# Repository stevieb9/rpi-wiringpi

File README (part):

NAME
    RPi::WiringPi - Perl interface to Raspberry Pi's board, GPIO, LCDs and
    other various items

SYNOPSIS
    Please see the FAQ for full usage details.

        use RPi::WiringPi;
        use RPi::Const qw(:all);
 
        my $pi = RPi::WiringPi->new;
 
        # For the below handful of system methods, see RPi::SysInfo
 
        my $mem_percent = $pi->mem_percent;
        my $cpu_percent = $pi->cpu_percent;
        my $cpu_temp    = $pi->core_temp;
        my $gpio_info   = $pi->gpio_info;
        my $raspi_conf  = $pi->raspi_config;
        my $net_info    = $pi->network_info;
        my $file_system = $pi->file_system;
        my $hw_details  = $pi->pi_details;
        my $pi_model    = $pi->pi_model;

        # Pin
 
        my $pin = $pi->pin(5);
        $pin->mode(OUTPUT);
        $pin->write(ON);
 
        my $num     = $pin->num;
        my $mode    = $pin->mode;
        my $state   = $pin->read;
 
        # Cleanup all pins and reset them to default before exiting your program
 
        $pi->cleanup;

DESCRIPTION
    This is the root module for the "RPi::WiringPi" system. It interfaces to
    a Raspberry Pi board, its accessories and its GPIO pins via the wiringPi
    <http://wiringpi.com> library through the Perl wrapper WiringPi::API
    <https://metacpan.org/pod/WiringPi::API> module, and various other
    custom device specific modules.

    wiringPi <http://wiringpi.com> must be installed prior to
    installing/using this module (v3.18).

    We always and only use the "GPIO" pin numbering scheme.

    This module is essentially a 'manager' for the sub-modules (ie.
    components). You can use the component modules directly, but retrieving
    components through this module instead has many benefits. We maintain a
    registry of pins and other data, and reset the Pi back to default
    settings when your program ends (on normal exit, on an uncaught die(),
    and on "SIGINT"/"SIGTERM"), so components are not left in an
    inconsistent state. Component modules do none of these things.

    There are a basic set of constants that can be imported. See RPi::Const.

    It's handy to have access to a pin mapping conversion chart. There's an
    excellent pin scheme map for reference at pinout.xyz
    <https://pinout.xyz/pinout/wiringpi>. You can also run the "pinmap"
    command that was installed by this module, or "wiringPi"'s "gpio
    readall" command.

BASE METHODS
  new([%args])
    Returns a new "RPi::WiringPi" object. We exclusively use the "GPIO"
    (Broadcom (BCM) GPIO) pin numbering scheme.

    Parameters:

        setup => $string

    Optional, String: Which "wiringPi" setup routine (and therefore pin
    numbering scheme) to initialize the board with. Matching is
    case-insensitive on the first letter:

        'gpio'      - GPIO (BCM) numbering; the default if not sent in
        'wiringpi'  - wiringPi's own (WPI) numbering
        'none'      - skip board setup entirely (the pin scheme remains
                      uninitialized; primarily for testing)

    Any other value will croak. Note that if another application in the
    process has already run a setup routine (signalled via the
    "RPI_PIN_MODE" environment variable), that existing scheme is honoured
    and this parameter is ignored.

        shm_key => $string

    By default, we use the key "rpiw" as the shared memory segment key. You
    can change this if desired. Useful for separating "groups" of Pi objects
    from one another (for example, production scripts can operate at the
    same time as test scripts, and both use their own shared memory pool).

        fatal_exit => $bool

    Optional: Controls what happens when we trap a "SIGINT" (Ctrl-C) or
    "SIGTERM". In both cases we first reset the Pi hardware to a safe state.
    By default ("fatal_exit" true), we then re-raise the signal so the
    program terminates as it normally would. Set "fatal_exit" to false (0)
    to perform the cleanup and then continue running your script (eg. for
    unit-test work, or to allow your own signal handling to take over).

    With multiple Pi objects in a single process, the signal is re-raised
    only if every live object has "fatal_exit" true; any object created with
    "fatal_exit => 0" keeps the process running.

    Note that this only affects trapped signals. Hardware cleanup on a
    normal exit or on an uncaught die() always happens automatically (via
    the object's "END"/ "DESTROY" handling); we do not trap $SIG{__DIE__},
    so a die() you catch yourself with "eval" will not disturb your pins.
    Any $SIG{INT}/$SIG{TERM} handler you installed before creating the
    object is chained to, not replaced.

        rpi_register => $bool

    Optional: Set this value to false (0) to bypass the Pi object
    registration in the meta data. This will also prevent pins from being
    registered as well. If set to false, no object or pin cleanup will take
    place at the end of a program run.

        rpi_register_pins => $bool

    Optional: Similar to "rpi_register", but only bypasses the pin
    registration. Object registration will still occur, and the object will
    be cleaned up after but the pins will not. Should only be used for
    testing.

  adc
    There are two different ADCs that you can select from. The default is
    the ADS1x15 series:

   ADS1115
    Returns a RPi::ADC::ADS object, which allows you to read the four analog
    input channels on an Adafruit ADS1xxx analog to digital converter.

    Parameters:

    The default (no parameters) is almost always enough, but please do
    review the documentation in the link above for further information, and
    have a look at the ADC tutorial section in this distribution.

   MCP3008
    You can also use an RPi::ADC::MCP3008 ADC.

    Parameters:

        model => 'MCP3008'

    Mandatory, String. The exact quoted string above.

        channel => $channel

    Mandatory, Integer. 0 or 1 for the Pi's onboard hardware CS/SS CE0 and
    CE1 pins, or any GPIO number above 1 in order to use an arbitrary GPIO
    pin for the CS pin, and we'll do the bit-banging of the SPI bus
    automatically.

  bmp
    Returns a RPi::BMP180 object, which allows you to return the current
    temperature in farenheit or celcius, along with the ability to retrieve
    the barometric pressure in kPa.

  dac
    Returns a RPi::DAC::MCP4922 object (supports all 49x2 series DACs).
    These chips provide analog output signals from the Pi's digital output.
    Please see the documentation of that module for further information on
    both the configuration and use of the DAC object.

    Parameters:

        model => 'MCP4922'

    Optional, String. The model of the DAC you're using. Defaults to
    "MCP4922".

        channel => 0|1

    Mandatory, Bool. The SPI channel to use.

        cs => $pin

    Mandatory, Integer. A valid GPIO pin that the DAC's Chip Select is
    connected to.

    There are a handful of other parameters that aren't required. For those,
    please refer to the RPi::DAC::MCP4922 documentation.

  dpot($cs, $channel)
    Returns a RPi::DigiPot::MCP4XXXX object, which allows you to manage a
    digital potentiometer (only the MCP4XXXX versions are currently
    supported).

    See the linked documentation for full documentation on usage, or the
    RPi::WiringPi::FAQ for usage examples.

  gps
    Returns a GPSD::Parse object, allowing you to track your location.

    The GPS distribution requires "gpsd" to be installed and running. All
    parameters for the GPS can be sent in here and we'll pass them along.
    Please see the link above for the full documentation on that module.

  hcsr04($trig, $echo)
    Returns a RPi::HCSR04 ultrasonic distance measurement sensor object,
    allowing you to retrieve the distance from the sensor in inches,
    centimetres or raw data.

    Parameters:

        $trig

    Mandatory, Integer: The trigger pin number, in GPIO numbering scheme.

        $echo

    Mandatory, Integer: The echo pin number, in GPIO numbering scheme.

  hygrometer($pin)
    Returns a RPi::DHT11 temperature/humidity sensor object, allows you to
    fetch the temperature (celcius or farenheit) as well as the current
    humidity level.

    Parameters:

        $pin

    Mandatory, Integer: The GPIO pin the sensor is connected to.

  i2c($addr, [$device])
    Creates a new RPi::I2C device object which allows you to communicate
    with the devices on an I2C bus.

    See the linked documentation for full documentation on usage, or the
    RPi::WiringPi::FAQ for usage examples.

    Aruino note: If using I2C with an Arduino, the Pi may speak faster than
    the Arduino can. If this is the case, try lowering the I2C bus speed on
    the Pi:

        dtparam=i2c_arm_baudrate=10000

  lcd(...)
    Returns a RPi::LCD object, which allows you to fully manipulate LCD
    displays connected to your Raspberry Pi.

    Please see the linked documentation for information regarding the
    parameters required.

  oled([$model], [$i2c_addr], [$display_splash_page])
    Returns a specific "RPi::OLED::SSD1306" OLED display object, allowing
    you to display text, characters and shapes to the screen.

    Currently, only the "128x64" size model is offered, see the
    RPi::OLED::SSD1306::128_64 documentation for full usage details.

    Parameters:

        $model

    Optional, String: The screen size of the OLED you've got. Valid options
    are "128x64", "128x32" and "96x16". Currently, only the "128x64" option
    is valid, and it's the default if not sent in.

        $i2c_addr

    Optional, Integer: The I2C address of your display. Defaults to 0x3C if
    not sent in.

        $display_splash_page

    Optional, Bool: Whether to display the splash page when the display is
    initialized. Defaults to true (1); send in 0 to skip it.

  pin($pin_num, $comment)
    Returns a RPi::Pin object, mapped to a specified GPIO pin, which you can
    then perform operations on. See that documentation for full usage
    details.

    Parameters:

        $pin_num

    Mandatory, Integer: The pin number to attach to.

        $comment

    Optional, String: A label stored alongside the pin's registration
    (visible in the metadata store and used by the test suite). Defaults to
    none.

  rtc
    Creates a new RPi::RTC::DS3231 object which provides access to the
    "DS3231" or "DS1307" real-time clock modules.

    See the linked documentation for full documentation on usage, or the
    RPi::WiringPi::FAQ for some usage examples.

    Parameters:

        $i2c_addr

    Optional, Integer: The I2C address of the RTC module. Defaults to 0x68
    for the "DS3231" unit.

  eeprom
    Creates and returns a new RPi::EEPROM::AT24C32 object for reading and
    writing to.

    See the linked documentation for full documentation on usage, parameters
    or the RPi::WiringPi::FAQ for some usage examples.

  expander
    Creates a new RPi::GPIOExpander::MCP23017 GPIO expander chip object.
    This adds an additional 16 pins across two banks (8 pins per bank).

    See the linked documentation for full documentation on usage, or the
    RPi::WiringPi::FAQ for some usage examples.

    Parameters:

        $i2c_addr

    Optional, Integer: The I2C address of the device. Defaults to 0x20.

        $expander

    Optional, String: The GPIO expander device type. Defaults to "MCP23017",
    and currently, this is the only option available.

  serial($device, $baud)
    Creates a new RPi::Serial object which allows basic read/write access to
    a serial bus.

    See the linked documentation for full documentation on usage, or the
    RPi::WiringPi::FAQ for usage examples.

    NOTE: On the Pi 3 and Pi 4, Bluetooth occupies the primary UART, leaving
    the header pins (14, 15) on the mini-UART ("/dev/ttyS0"). To put the
    full PL011 UART back on the header you must disable Bluetooth in the
    "/boot/firmware/config.txt" file ("/boot/config.txt" on releases before
    Bookworm):

        dtoverlay=pi3-disable-bt-overlay

    On the Pi 5, Bluetooth has its own dedicated UART, so no "disable-bt"
    overlay is needed; simply enable the header UART ("/dev/ttyAMA0") with
    "enable_uart=1".

  servo($pin_num)
    This method configures PWM clock and divisor to operate a typical 50Hz
    servo, and returns a special RPi::Pin object. These servos have a "left"
    pulse of 50, a "centre" pulse of 150 and a "right" pulse of 250. On exit
    of the program (or a crash), we automatically clean everything up
    properly.

    Parameters:

        $pin_num

    Mandatory, Integer: The pin number (technically, this *must* be 18 on
    the Raspberry Pi 3, as that's the only hardware PWM pin.

        %pwm_config

    Optional, Hash. This parameter should only be used if you know what
    you're doing and are having very specific issues.

    Keys are "clock" with a value that coincides with the PWM clock speed.
    It defaults to 192. The other key is "range", the value being an integer
    that sets the range of the PWM. Defaults to 2000.

    Example:

        my $servo = $pi->servo(18);
 
        $servo->pwm(50);  # all the way left
        $servo->pwm(250); # all the way right

  shift_register($base, $num_pins, $data, $clk, $latch)
    Allows you to access the output pins of up to four 74HC595 shift
    registers in series, for a total of eight new output pins per register.
    Numerous chains of four registers are permitted, each chain uses three
    GPIO pins.

    Parameters:

        $base

    Mandatory: Integer, represents the number at which you want to start
    referencing the new output pins attached to the register(s). For
    example, if you use 100 here, output pin 0 of the register will be 100,
    output 1 will be 101 etc.

        $num_pins

    Mandatory: Integer, the number of output pins on the registers you want
    to use. Each register has eight outputs, so if you have a single
    register in use, the maximum number of additional pins would be eight.

        $data

    Mandatory: Integer, the GPIO pin number attached to the "DS" pin (14) on
    the shift register.

        $clk

    Mandatory: Integer, the GPIO pin number attached to the "SHCP" pin (11)
    on the shift register.

        $latch

    Mandatory: Integer, the GPIO pin number attached to the "STCP" pin (12)
    on the shift register.

  spi($channel, $speed)
    Creates a new RPi::SPI object which allows you to communicate on the
    Serial Peripheral Interface (SPI) bus with attached devices.

    See the linked documentation for full documentation on usage, or the
    RPi::WiringPi::FAQ for usage examples.

  stepper_motor($pins)
    Creates a new RPi::StepperMotor object which allows you to drive a
    28BYJ-48 stepper motor with a ULN2003 driver chip.

    See the linked documentation for full usage instructions and the
    optional parameters.

    Parameters:

        pins => $aref

    Mandatory, Array Reference: The ULN2003 has four data pins, IN1, IN2,
    IN3 and IN4. Send in the GPIO pin numbers in the array reference which
    correlate to the driver pins in the listed order.

        speed => 'half'|'full'

    Optional, String: By default we run in "half speed" mode. Essentially,
    in this mode we run through all eight steps. Send in 'full' to double
    the speed of the motor. We do this by skipping every other step.

        delay => Float|Int

    Optional, Float or Int: By default, between each step, we delay by 0.01
    seconds. Send in a float or integer for the number of seconds to delay
    each step by. The smaller this number, the faster the motor will turn.

  CORE PI SYSTEM METHODS
    Core methods are inherited in and documented in RPi::WiringPi::Core. See
    that documentation for full details of each one. I've included a basic
    description of them here.

   gpio_layout
    Returns the GPIO layout, which in essence is the Pi board revision
    number.

   io_led
    Turn the disk IO (green) LED on or off.

   pwr_led
    Turn the power (red) LED on or off.

   identify
    Toggles the power led off and disk IO led on which allows external
    physical identification of the Pi you're running on.

   label
    Sets an internal label/name to your RPi::WiringPi Pi object.

   pin_scheme
    Returns the current pin mapping scheme in use within the object.

   pin_map
    Returns a hash reference mapping of the physical pin numbers to a pin
    scheme's pin numbers.

   pin_to_gpio
    Converts a pin number from any non-GPIO (BCM) scheme to GPIO (BCM)
    scheme.

   wpi_to_gpio
    Converts a wiringPi pin number to GPIO pin number.

   phys_to_gpio
    Converts a physical pin number to the GPIO pin number.

   pwm_range
    Set/get the PWM range.

   pwm_mode
    Set/get the PWM mode.

   pwm_clock
    Set/get the PWM clock.

   registered_pins
    Returns an array reference of all pin numbers currently registered in
    the system. Used primarily for cleanup functionality.

   register_pin
    Registers a pin with the system for error checking, and proper resetting
    in the cleanup routines.

   unregister_pin
    Removes an already registered pin.

   cleanup
    Cleans up the entire system, resetting all pins and devices back to the
    state we found them in when we initialized the system. It also releases
    any armed interrupts (via WiringPi::API::stop_interrupts()) - stopping
    the wiringPi ISR threads and closing the event pipe - so you don't have
    to do that yourself at teardown.

    Only the process that created the object performs the cleanup: in a
    forked child the call is a no-op, so a child can't reset pins or mutate
    the shared metadata on the parent's behalf when it exits.

  ADDITIONAL PI SYSTEM METHODS
    We also include in the Pi object several hardware-type methods brought
    in from RPi::SysInfo. They are loaded through RPi::WiringPi::Core via
    inheritance. See the RPi::SysInfo documentation for full method details.

        my $mem_percent = $pi->mem_percent;
        my $cpu_percent = $pi->cpu_percent;
        my $cpu_temp    = $pi->core_temp;
        my $gpio_info   = $pi->gpio_info;
        my $raspi_conf  = $pi->raspi_config;
        my $net_info    = $pi->network_info;
        my $file_system = $pi->file_system;
        my $hw_details  = $pi->pi_details;

   cpu_percent
    Returns the current CPU usage.

   mem_percent
    Returns the current memory usage.

   core_temp
    Returns the current temperature of the CPU core.

   gpio_info
    Returns the current status and configuration of one, many or all of the
    GPIO pins.

   raspi_config
    Returns the live "vcgencmd get_config" values plus the non-comment
    directives from the active "config.txt" ("/boot/firmware/config.txt" on
    Bookworm and later, falling back to "/boot/config.txt" on older
    releases).

   network_info
    Returns the network configuration of the Pi, via "ifconfig" where the
    "net-tools" package is installed, falling back to "ip addr" where it is
    not (as on current Raspberry Pi OS Lite).

   file_system
    Returns current disk and mount information.

   pi_details
    Returns various information on both the hardware and OS aspects of the
    Pi.

   pi_model
    Returns the normalized Raspberry Pi board name (eg. "Raspberry Pi 5
    Model B Rev 1.1"), read from the devicetree model with a "/proc/cpuinfo"
    revision-code decode fallback. Works across the Pi 0 through 5.

  INTERRUPT METHODS
    Arm an interrupt on a pin with "$pin->set_interrupt($edge, $callback)"
    (see RPi::Pin). As of "WiringPi::API" 3.18 the callback must be a code
    reference, and it runs in your own interpreter when you service the
    interrupt rather than in the wiringPi ISR thread. The following methods
    drive that dispatch. See Interrupt usage in the FAQ for a complete
    example.

   wait_interrupts($timeout_ms)
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
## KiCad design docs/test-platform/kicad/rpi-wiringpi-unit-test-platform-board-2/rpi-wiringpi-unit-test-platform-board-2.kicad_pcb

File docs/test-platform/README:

RPi::WiringPi test platform — docs/test-platform/ guide

Everything in this directory describes the unit-test hardware platform and is
GENERATED from a single source of truth. Do not hand-edit the generated files;
edit the source and regenerate (see below).

The full technical reference — the pin map, buses, loop-backs, default pin
states, collisions and power rails — is test-pinout-doc.md. This README is only
the regeneration runbook and a manifest of what each file is. It deliberately
carries NO pin data, so it cannot drift.

# Source of truth

  scripts/helpers/board-model.py        THE canonical electrical model
                                        (COMPONENTS / NETS / J1FUNC / DRIVER /
                                        POWER / SHEETS). Edit this to change the
                                        board; the schematic, KiCad project,
                                        netlist and pin doc all render from it.

  scripts/helpers/model-from-tests.py   an INDEPENDENT re-derivation of the same
                                        model from the test suite. It is diffed
                                        against board-model.py as a drift gate -
                                        if they disagree, one is stale.

  docs/test-platform/test-pinout-doc.tmpl.md
                                        the pin doc's prose/art template. Its one
                                        generated block - the section 12 Pi 5
                                        default-state table - comes from
                                        t/RPiTest.pm. Edit the template (not the
                                        rendered .md) for prose changes.

# Regenerate

The schematic Python venv is built automatically on first run; you also need
`netlistsvg` (Node) for the schematic PDF. Then:

    perl scripts/gen-test-platform.pl

It runs the Python generators in a throwaway scratch tree and files the
artifacts into this directory: the pinout JPEGs, the netlist, the multi-page
schematic PDFs, and the rendered pin doc. The wire-routed SVGs are scratch
intermediates (they feed the PDF) and are not kept. It never writes to the
repo's t/, nor to kicad/ - the KiCad board projects are scaffolded separately
(see "KiCad boards" below).

To regenerate *all* derived docs at once - these test-platform artifacts plus
the POD->markdown replicas and the FAQ test-table - run `make regen_docs`
instead (see `scripts/README.md`). That target also runs automatically as part
of `make dist`.

# Drift gate (runs under `make test`)

t/04-test-platform-model.t fails the build when:
  - model-from-tests.py has drifted from board-model.py,
  - any populated, non-frozen KiCad board project no longer validates,
  - a blessed board changed without a re-bless (check-board-locks.py),
  - a board that still has a model no longer implements it pin-for-pin
    (check-board-nets.py),
  - a board model disagrees with the IC datasheets - ALL-STOP
    (check-datasheets.py), or
  - test-pinout-doc.md is stale versus its template + sources.

Run the checks directly:
    python3 scripts/helpers/check-model-drift.py
    python3 scripts/helpers/check-board-locks.py
    python3 scripts/helpers/check-board-nets.py
    python3 scripts/helpers/check-datasheets.py
    python3 scripts/helpers/render-doc.py --check

# KiCad boards

The unit-test platform is five separate PCBs, each a self-contained KiCad
project in its own subdirectory of kicad/:

  kicad/rpi-wiringpi-unit-test-platform-board-1/  board 1 (Pi host, planned last)
  kicad/rpi-wiringpi-unit-test-platform-board-2/  board 2 (finalized & ordered)
  kicad/rpi-wiringpi-unit-test-platform-board-3/  board 3 (finalized & ordered)
  kicad/rpi-wiringpi-unit-test-platform-board-4/  board 4 (finalized & ordered)
  kicad/rpi-wiringpi-unit-test-platform-board-5/  board 5 (finalized & ordered)

These are NOT regenerated by gen-test-platform.pl. Each board is scaffolded
ONCE with gen-kicad.py, then hand-finalized in KiCad:

    python3 scripts/helpers/gen-kicad.py docs/test-platform/kicad/<board-dir> \
        [--model scripts/helpers/board-N-model.py]

That writes a stand-alone <board>.kicad_sch / .kicad_pro / fp-lib-table /
<board>.pretty into the directory (project name defaults to the directory's
basename; --model selects a per-board model, default board-model.py). It refuses
to overwrite an existing project, so a hand-edited board is never clobbered. The
drift gate validates every populated, non-frozen board; empty placeholders (no
.kicad_sch yet) are skipped.

Once a board is hand-finalized it becomes the source of truth for itself: it is
"blessed" (check-board-locks.py --bless <board-dir>) to freeze every design file
byte-for-byte, and listed in %FROZEN in t/04-test-platform-model.t so the
KiCad-validation step leaves it alone. Boards 2, 3, 4 and 5 are finalized this
way and have NO generated model (they are authoritative as their own KiCad
files).

# Manifest (what each entry is, and what produces it)

  README                          this guide                         (hand)
  test-pinout-doc.md              full pin/wiring reference          <- render-doc.py
  test-pinout-doc.tmpl.md         its source template                (hand + generated)
  test-pinout-overview.jpg        bus/block pinout image             <- gen-pinout-images.py
  test-pinout-detail.jpg          pin-by-pin pinout image            <- gen-pinout-images.py
  test-platform-schematic-A3.pdf  multi-page schematic (A3, print)   <- gen-schematic.py -> netlistsvg -> gen-pdf.py
  test-platform-schematic-A4.pdf  multi-page schematic (A4)          <- (same chain)
  kicad/                          per-board KiCad projects, scaffolded <- gen-kicad.py
                                  once then hand-managed (see "KiCad      (one-shot)
                                  boards" above)

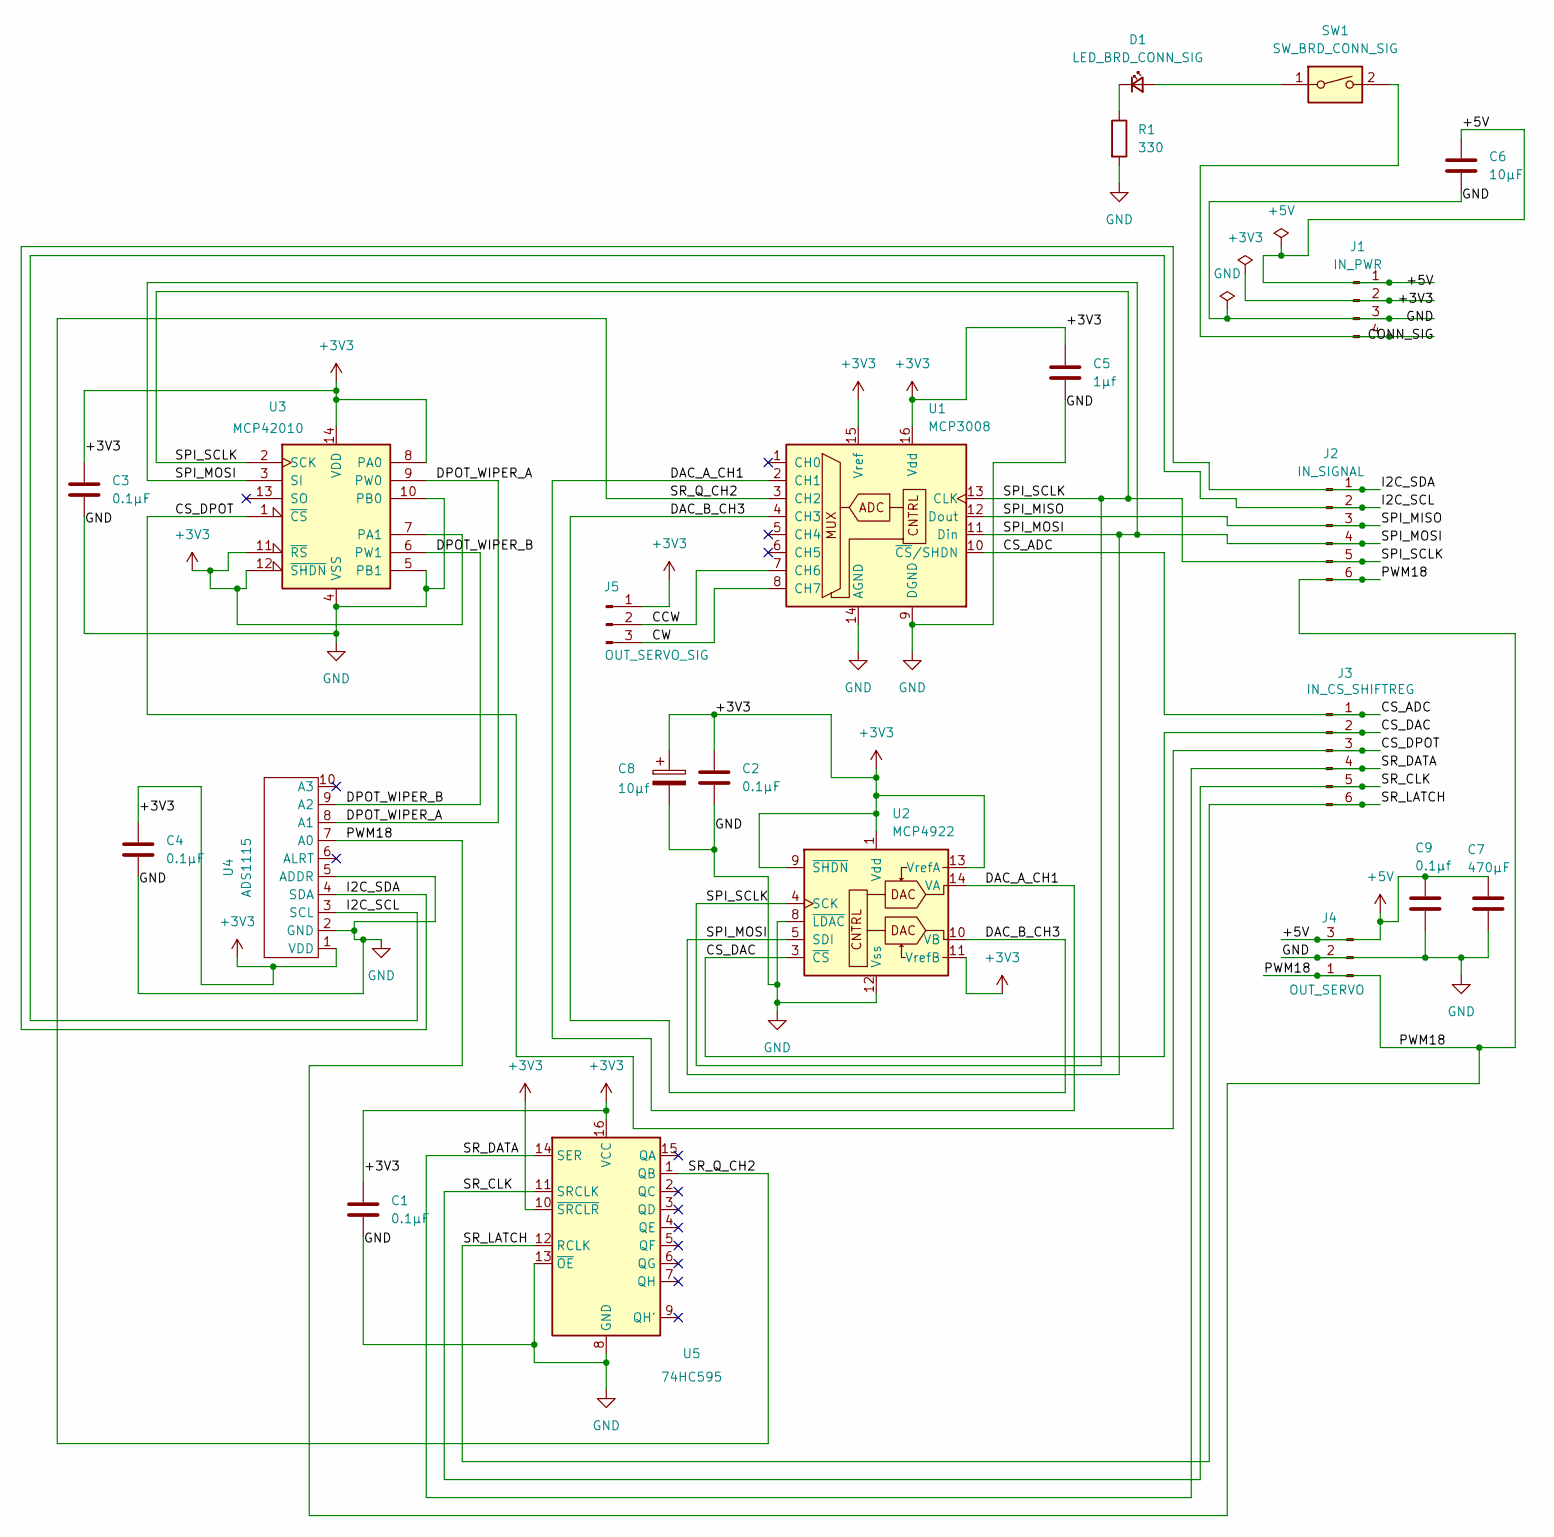
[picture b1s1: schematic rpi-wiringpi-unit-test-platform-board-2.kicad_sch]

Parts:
C1, C2, C3, C4: 0.1µF; C_Disc_D3.0mm_W2.0mm_P2.50mm
C5: 1µf; C_Disc_D3.0mm_W2.0mm_P2.50mm
C6: 10µF; CP_Radial_D5.0mm_P2.50mm
C7: 470µF; CP_Radial_D8.0mm_P2.50mm
C8: 10µf; CP_Radial_Tantal_D5.0mm_P2.50mm
C9: 0.1µf; C_Disc_D3.0mm_W2.0mm_P2.50mm
D1: LED_BRD_CONN_SIG; LED_D5.0mm
J1: IN_PWR; JST_XH_B4B-XH-A_1x04_P2.50mm_Vertical
J2: IN_SIGNAL; JST_XH_B6B-XH-A_1x06_P2.50mm_Vertical
J3: IN_CS_SHIFTREG; JST_XH_B6B-XH-A_1x06_P2.50mm_Vertical
J4: OUT_SERVO; JST_XH_B3B-XH-A_1x03_P2.50mm_Vertical
J5: OUT_SERVO_SIG; JST_XH_B3B-XH-A_1x03_P2.50mm_Vertical
R1: 330; R_Axial_DIN0207_L6.3mm_D2.5mm_P7.62mm_Horizontal
SW1: SW_BRD_CONN_SIG; SW_DIP_SPSTx01_Slide_9.78x4.72mm_W7.62mm_P2.54mm
U1: MCP3008; DIP-16_W7.62mm
U2: MCP4922; DIP-14_W7.62mm
U3: MCP42010; DIP-14_W7.62mm
U4: ADS1115; ADS1115_Breakout
U5: 74HC595; DIP-16_W7.62mm

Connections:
+3V3: C1.1, C2.1, C3.1, C4.1, C5.1, C8.1, J1.2, J5.1, U1.15 (Vref), U1.16 (Vdd), U2.1 (Vdd), U2.9 (~SHDN), U2.11 (VrefB), U2.13 (VrefA), U3.7 (PA1), U3.8 (PA0), U3.11 (~RS), U3.12 (~SHDN), U3.14 (VDD), U4.1 (VDD), U5.10 (~SRCLR), U5.16 (VCC)
+5V: C6.1, C7.1, C9.1, J1.1, J4.3
/CCW: J5.2, U1.7 (CH6)
/CONN_SIG: J1.4, SW1.2
/CS_ADC: J3.1, U1.10 (~CS/SHDN)
/CS_DAC: J3.2, U2.3 (~CS)
/CS_DPOT: J3.3, U3.1 (~CS)
/CW: J5.3, U1.8 (CH7)
/DAC_A_CH1: U1.2 (CH1), U2.14 (VA)
/DAC_B_CH3: U1.4 (CH3), U2.10 (VB)
/DPOT_WIPER_A: U3.9 (PW0), U4.8 (A1)
/DPOT_WIPER_B: U3.6 (PW1), U4.9 (A2)
/I2C_SCL: J2.2, U4.3 (SCL)
/I2C_SDA: J2.1, U4.4 (SDA)
/PWM18: J2.6, J4.1, U4.7 (A0)
/SPI_MISO: J2.3, U1.12 (Dout)
/SPI_MOSI: J2.4, U1.11 (Din), U2.5 (SDI), U3.3 (SI)
/SPI_SCLK: J2.5, U1.13 (CLK), U2.4 (SCK), U3.2 (SCK)
/SR_CLK: J3.5, U5.11 (SRCLK)
/SR_DATA: J3.4, U5.14 (SER)
/SR_LATCH: J3.6, U5.12 (RCLK)
/SR_Q_CH2: U1.3 (CH2), U5.1 (QB)
GND: C1.2, C2.2, C3.2, C4.2, C5.2, C6.2, C7.2, C8.2, C9.2, J1.3, J4.2, R1.2, U1.9 (DGND), U1.14 (AGND), U2.8 (~LDAC), U2.12 (Vss), U3.4 (VSS), U3.5 (PB1), U3.10 (PB0), U4.2 (GND), U4.5 (ADDR), U5.8 (GND), U5.13 (~OE)
unnamed: D1.2 (A), SW1.1
unnamed: D1.1 (K), R1.1

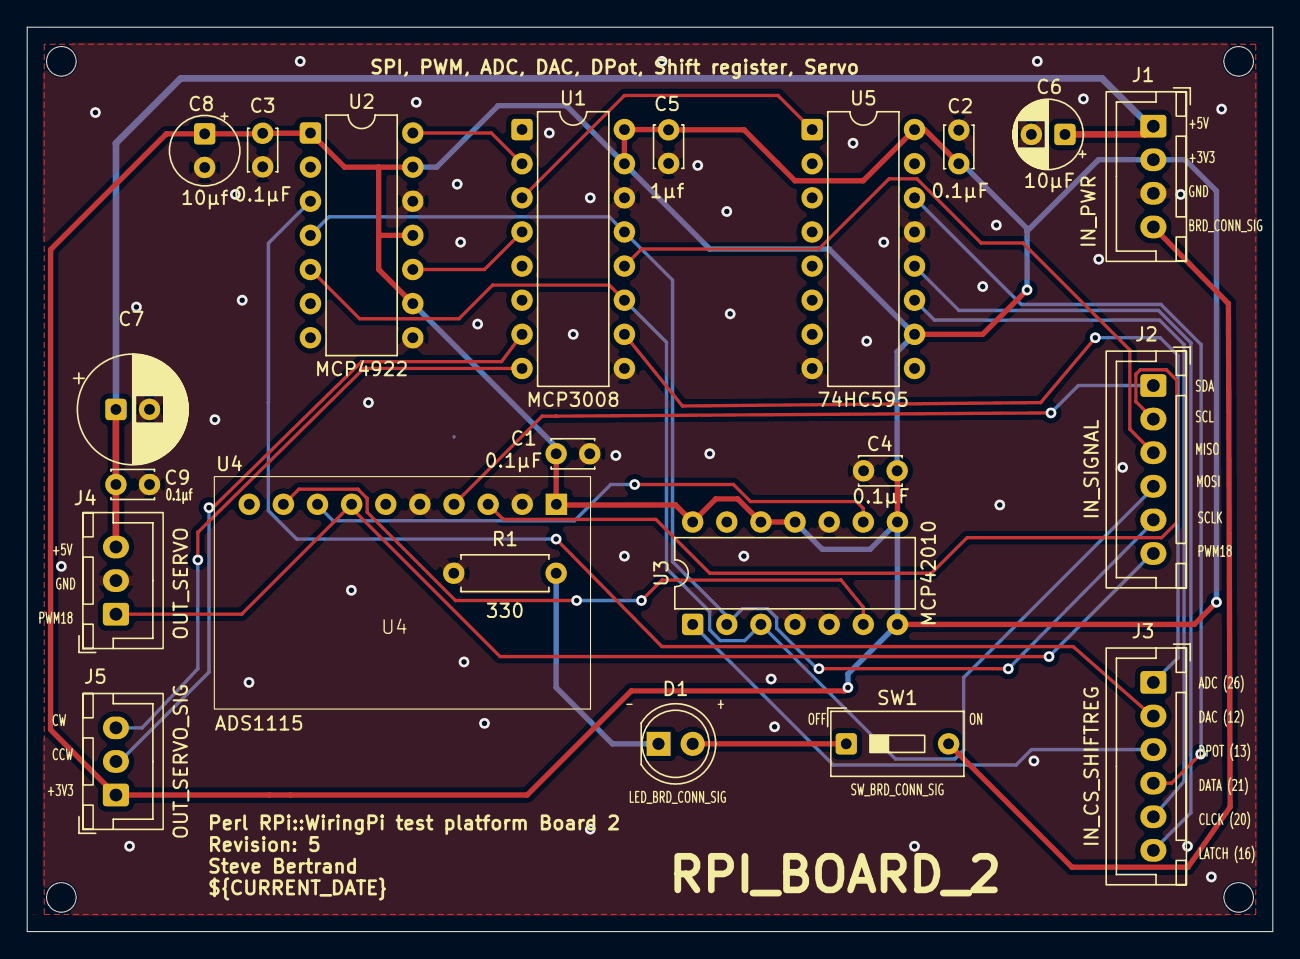
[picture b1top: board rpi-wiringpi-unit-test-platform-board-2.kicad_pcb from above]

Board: 2 copper layers, 92.7 x 67.3 mm, 22 parts (0 on the bottom side), 25 nets.

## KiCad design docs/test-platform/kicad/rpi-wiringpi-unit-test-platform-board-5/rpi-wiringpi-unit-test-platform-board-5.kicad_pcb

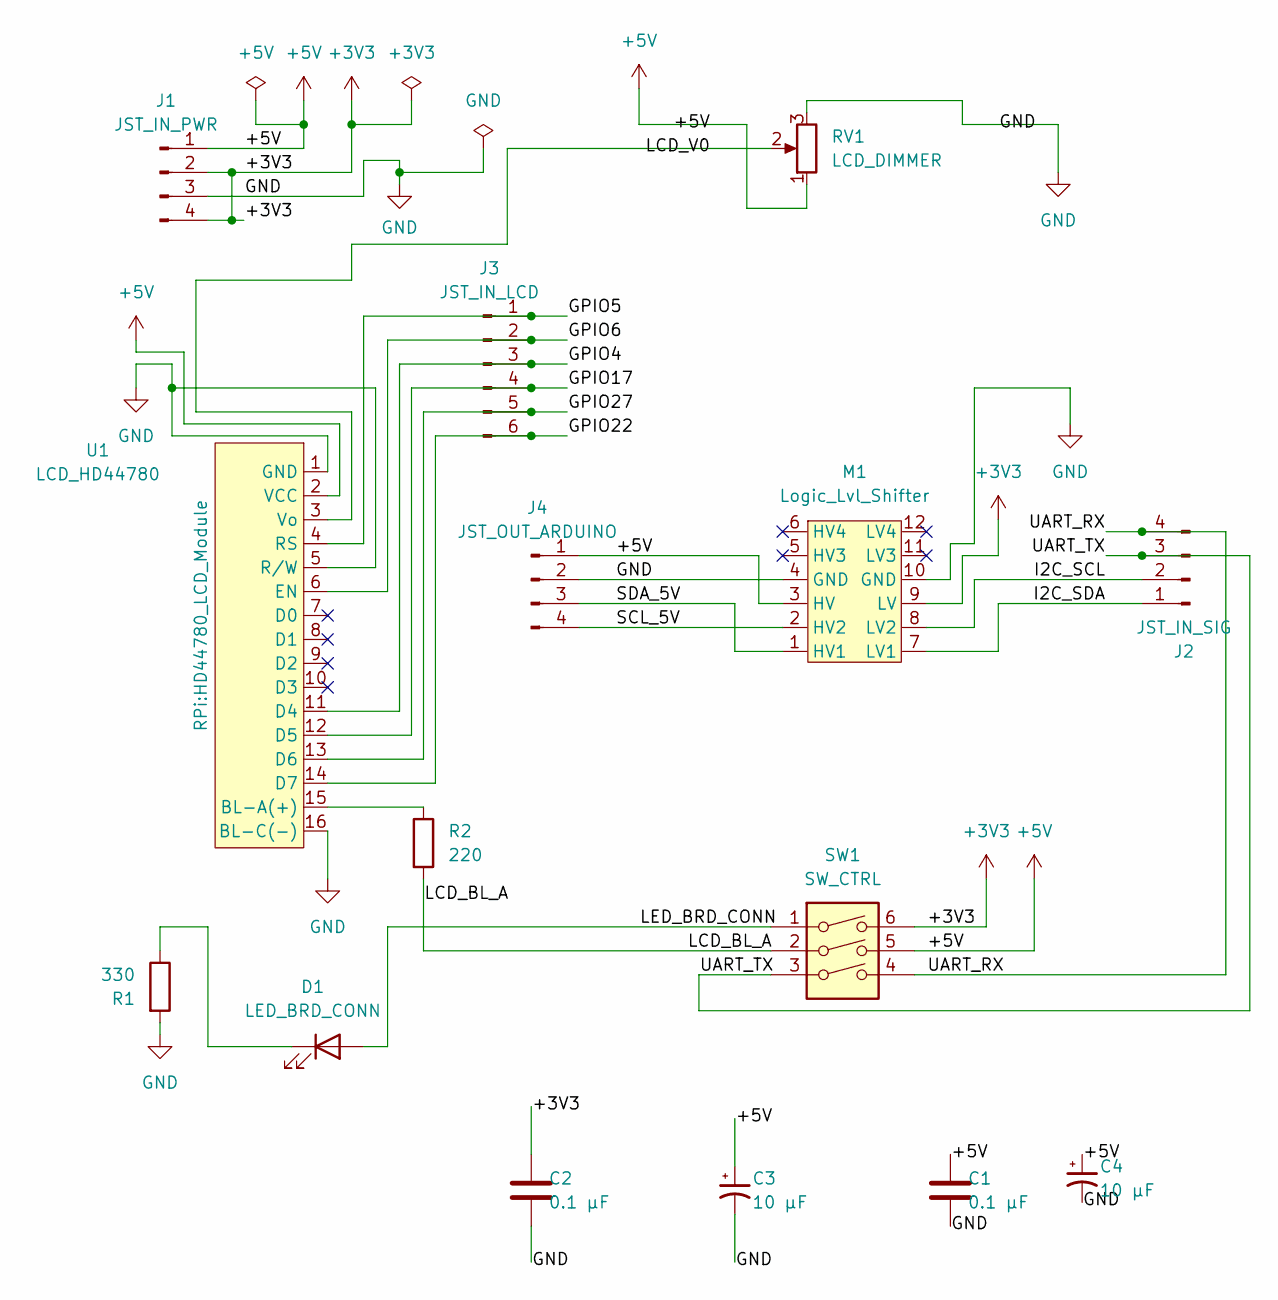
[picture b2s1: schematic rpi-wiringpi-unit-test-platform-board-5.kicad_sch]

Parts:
C1, C2: 0.1 µF; C_Disc_D5.0mm_W2.5mm_P2.50mm
C3, C4: 10 µF; CP_Radial_D5.0mm_P2.50mm
D1: LED_BRD_CONN; LED_D5.0mm
J1: JST_IN_PWR; JST_XH_B4B-XH-A_1x04_P2.50mm_Vertical
J2: JST_IN_SIG; JST_XH_B4B-XH-A_1x04_P2.50mm_Vertical
J3: JST_IN_LCD; JST_XH_B6B-XH-A_1x06_P2.50mm_Vertical
J4: JST_OUT_ARDUINO; JST_XH_B4B-XH-A_1x04_P2.50mm_Vertical
M1: Logic_Lvl_Shifter; Level_Converter_4_Pin
R1: 330; R_Axial_DIN0207_L6.3mm_D2.5mm_P7.62mm_Horizontal
R2: 220; R_Axial_DIN0207_L6.3mm_D2.5mm_P7.62mm_Horizontal
RV1: LCD_DIMMER; Potentiometer_Alps_RK09K_Single_Vertical
SW1: SW_CTRL; SW_DIP_SPSTx03_Slide_9.78x9.8mm_W7.62mm_P2.54mm
U1: LCD_HD44780; HD44780_LCD_Module

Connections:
+3V3: C2.1, J1.2, J1.4, M1.9 (LV), SW1.6
+5V: C1.1, C3.1, C4.1, J1.1, J4.1, M1.3 (HV), RV1.1, SW1.5, U1.2 (VCC)
/GPIO4: J3.3, U1.11 (D4)
/GPIO5: J3.1, U1.4 (RS)
/GPIO6: J3.2, U1.6 (EN)
/GPIO17: J3.4, U1.12 (D5)
/GPIO22: J3.6, U1.14 (D7)
/GPIO27: J3.5, U1.13 (D6)
/I2C_SCL: J2.2, M1.8 (LV2)
/I2C_SDA: J2.1, M1.7 (LV1)
/LCD_BL_A: R2.2, SW1.2
/LCD_V0: RV1.2, U1.3 (Vo)
/LED_BRD_CONN: D1.2 (A), SW1.1
/SCL_5V: J4.4, M1.2 (HV2)
/SDA_5V: J4.3, M1.1 (HV1)
/UART_RX: J2.4, SW1.4
/UART_TX: J2.3, SW1.3
GND: C1.2, C2.2, C3.2, C4.2, J1.3, J4.2, M1.4 (GND), M1.10 (GND), R1.2, RV1.3, U1.1 (GND), U1.5 (R/W), U1.16 (BL-C(-))
unnamed: D1.1 (K), R1.1
unnamed: R2.1, U1.15 (BL-A(+))

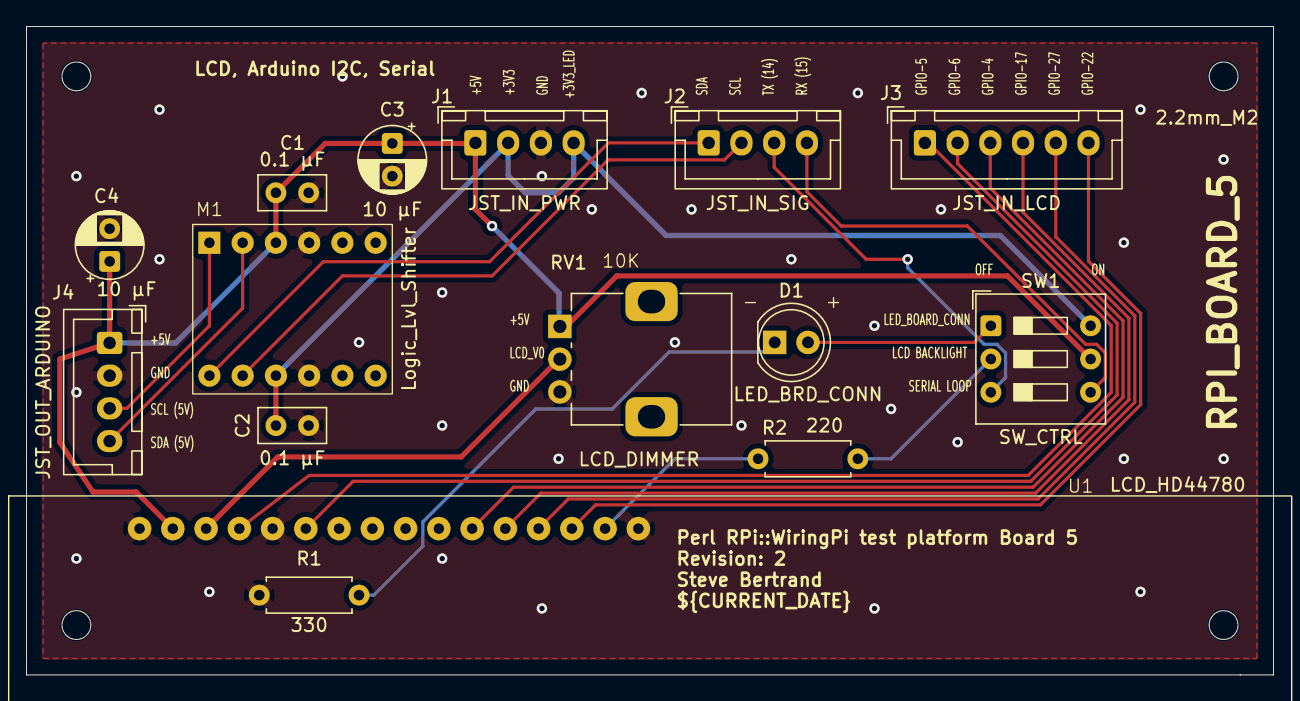
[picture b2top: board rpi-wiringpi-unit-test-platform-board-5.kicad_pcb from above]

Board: 2 copper layers, 95.2 x 49.5 mm, 15 parts (0 on the bottom side), 20 nets.

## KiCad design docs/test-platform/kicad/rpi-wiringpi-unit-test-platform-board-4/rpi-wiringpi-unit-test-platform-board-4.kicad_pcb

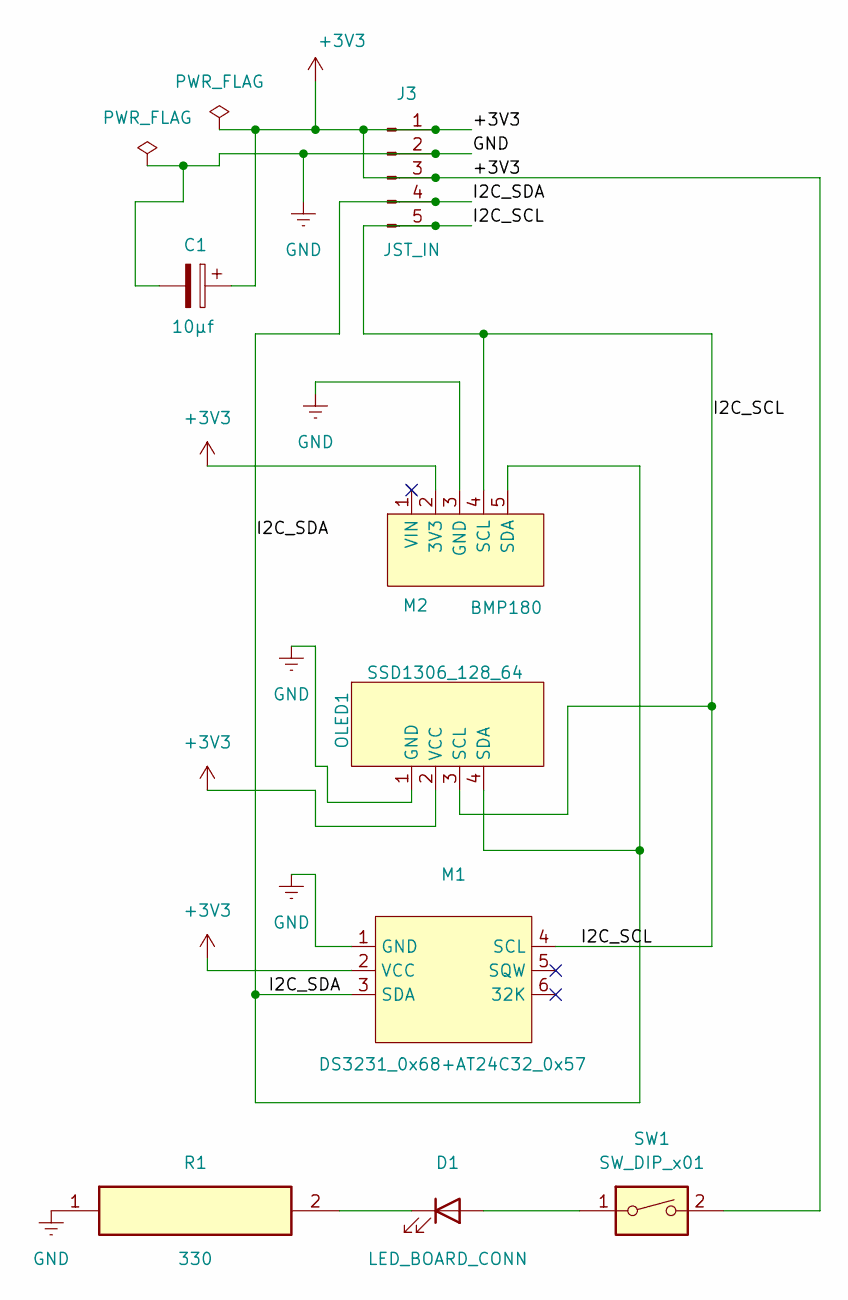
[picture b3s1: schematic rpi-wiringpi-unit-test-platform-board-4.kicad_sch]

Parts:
C1: 10µf; CP_Radial_D5.0mm_P2.50mm
D1: LED_BOARD_CONN; LED_D5.0mm
J3: JST_IN; JST_XH_B5B-XH-A_1x05_P2.50mm_Vertical
M1: DS3231_0x68+AT24C32_0x57; DS3231
M2: BMP180
OLED1: SSD1306_128_64; OLED_SSD_1306_128_64
R1: 330; R_Axial_DIN0207_L6.3mm_D2.5mm_P7.62mm_Horizontal
SW1: SW_DIP_x01; SW_DIP_SPSTx01_Slide_9.78x4.72mm_W7.62mm_P2.54mm

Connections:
+3V3: C1.1, J3.1, J3.3, M1.2 (VCC), M2.2 (3V3), OLED1.2 (VCC), SW1.2
/I2C_SCL: J3.5, M1.4 (SCL), M2.4 (SCL), OLED1.3 (SCL)
/I2C_SDA: J3.4, M1.3 (SDA), M2.5 (SDA), OLED1.4 (SDA)
GND: C1.2, J3.2, M1.1 (GND), M2.3 (GND), OLED1.1 (GND), R1.1
unnamed: D1.2 (A), SW1.1
unnamed: D1.1 (K), R1.2

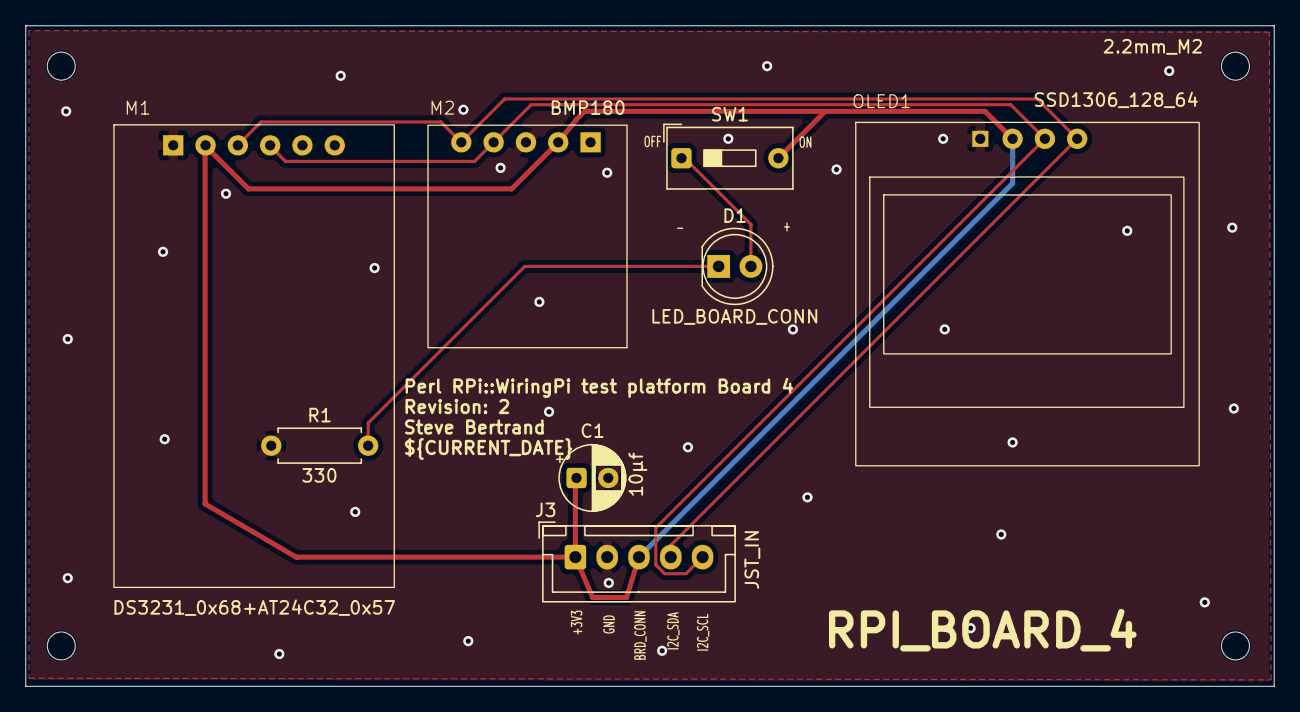
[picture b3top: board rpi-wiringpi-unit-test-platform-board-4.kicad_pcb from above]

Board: 2 copper layers, 98.2 x 51.9 mm, 8 parts (0 on the bottom side), 6 nets.

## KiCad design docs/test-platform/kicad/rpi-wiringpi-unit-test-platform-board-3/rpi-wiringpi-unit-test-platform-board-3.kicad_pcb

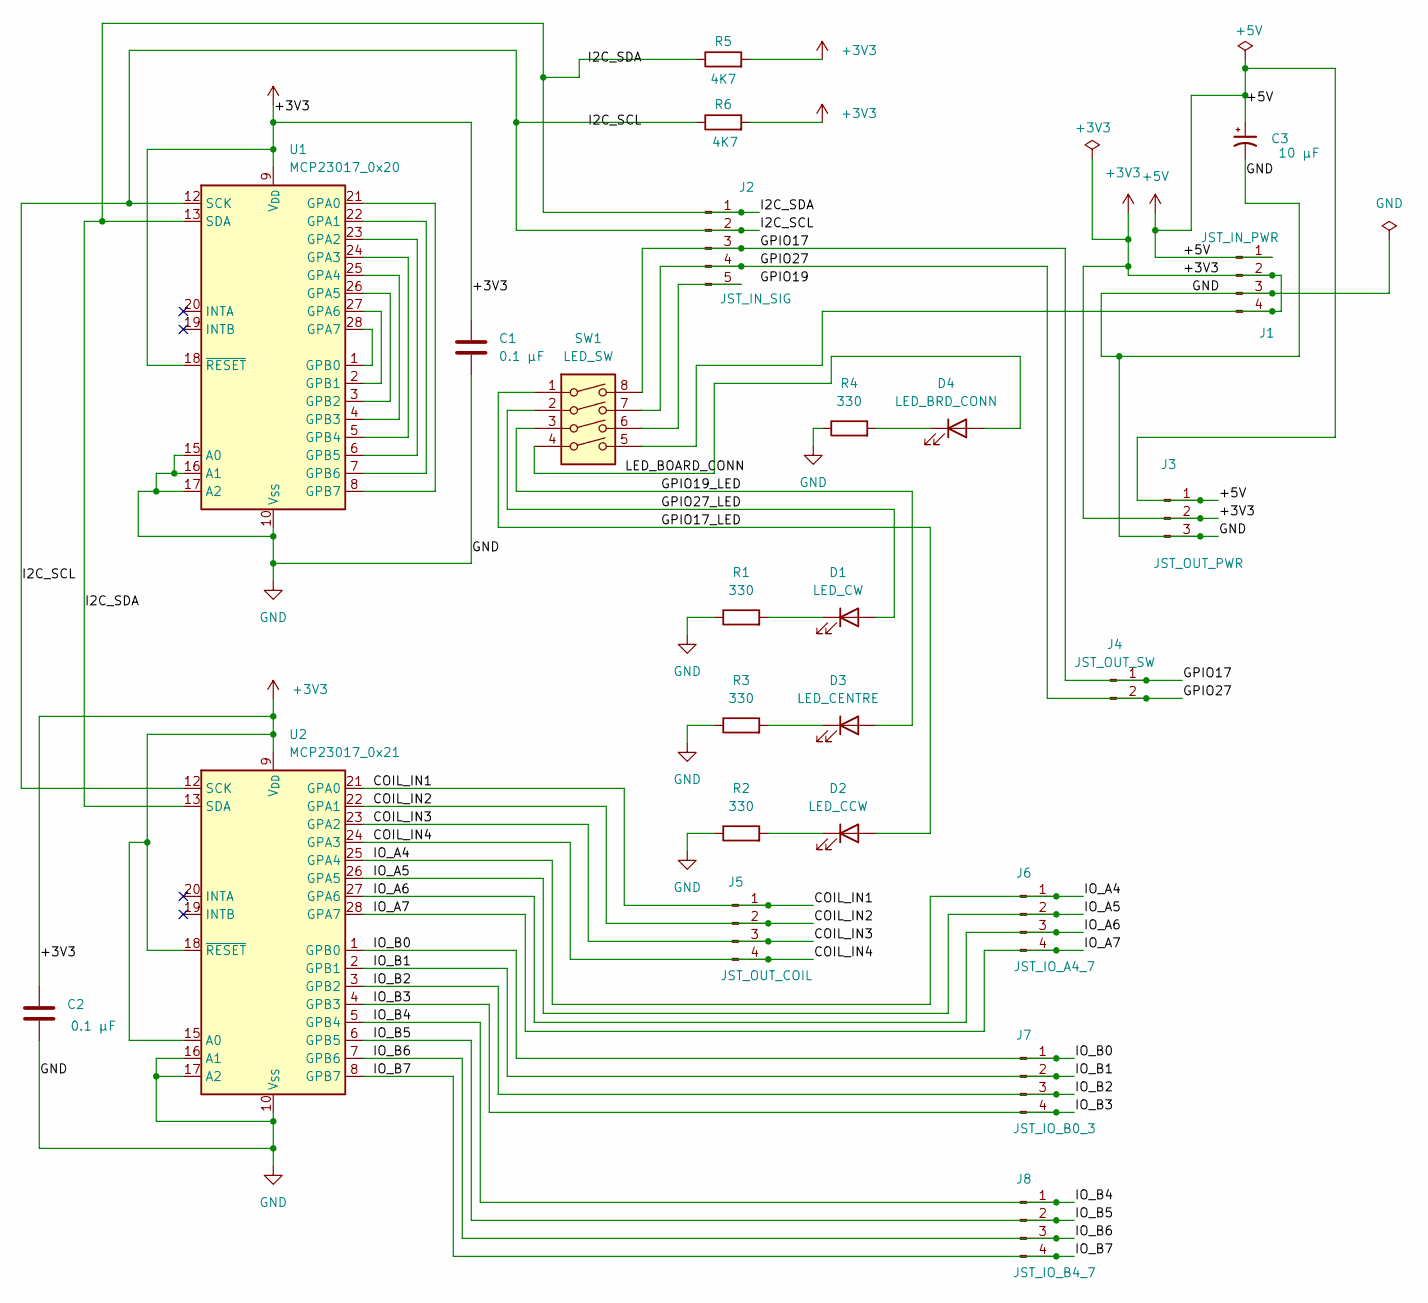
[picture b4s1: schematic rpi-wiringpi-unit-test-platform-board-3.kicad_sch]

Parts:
C1, C2: 0.1 µF; C_Disc_D5.0mm_W2.5mm_P2.50mm
C3: 10 µF; CP_Radial_D5.0mm_P2.50mm
D1: LED_CW; LED_D5.0mm
D2: LED_CCW; LED_D5.0mm
D3: LED_CENTRE; LED_D5.0mm
D4: LED_BRD_CONN; LED_D5.0mm
J1: JST_IN_PWR; JST_XH_B4B-XH-A_1x04_P2.50mm_Vertical
J2: JST_IN_SIG; JST_XH_B5B-XH-A_1x05_P2.50mm_Vertical
J3: JST_OUT_PWR; JST_XH_B3B-XH-A_1x03_P2.50mm_Vertical
J4: JST_OUT_SW; JST_XH_B2B-XH-A_1x02_P2.50mm_Vertical
J5: JST_OUT_COIL; JST_XH_B4B-XH-A_1x04_P2.50mm_Vertical
J6: JST_IO_A4_7; JST_XH_B4B-XH-A_1x04_P2.50mm_Vertical
J7: JST_IO_B0_3; JST_XH_B4B-XH-A_1x04_P2.50mm_Vertical
J8: JST_IO_B4_7; JST_XH_B4B-XH-A_1x04_P2.50mm_Vertical
R1, R2, R3, R4: 330; R_Axial_DIN0207_L6.3mm_D2.5mm_P7.62mm_Horizontal
R5, R6: 4K7; R_Axial_DIN0207_L6.3mm_D2.5mm_P7.62mm_Horizontal
SW1: LED_SW; SW_DIP_SPSTx04_Slide_6.7x11.72mm_W7.62mm_P2.54mm_LowProfile
U1: MCP23017_0x20; DIP-28_W7.62mm
U2: MCP23017_0x21; DIP-28_W7.62mm

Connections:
+3V3: C1.1, C2.1, J1.2, J1.4, J3.2, R5.2, R6.2, SW1.5, U1.9 (V_{DD}), U1.18 (~RESET), U2.9 (V_{DD}), U2.15 (A0), U2.18 (~RESET)
+5V: C3.1, J1.1, J3.1
/COIL_IN1: J5.1, U2.21 (GPA0)
/COIL_IN2: J5.2, U2.22 (GPA1)
/COIL_IN3: J5.3, U2.23 (GPA2)
/COIL_IN4: J5.4, U2.24 (GPA3)
/GPIO17: J2.3, J4.1, SW1.8
/GPIO17_LED: D2.2 (A), SW1.1
/GPIO19_LED: D3.2 (A), SW1.3
/GPIO27: J2.4, J4.2, SW1.7
/GPIO27_LED: D1.2 (A), SW1.2
/I2C_SCL: J2.2, R6.1, U1.12 (SCK), U2.12 (SCK)
/I2C_SDA: J2.1, R5.1, U1.13 (SDA), U2.13 (SDA)
/IO_A4: J6.1, U2.25 (GPA4)
/IO_A5: J6.2, U2.26 (GPA5)
/IO_A6: J6.3, U2.27 (GPA6)
/IO_A7: J6.4, U2.28 (GPA7)
/IO_B0: J7.1, U2.1 (GPB0)
/IO_B1: J7.2, U2.2 (GPB1)
/IO_B2: J7.3, U2.3 (GPB2)
/IO_B3: J7.4, U2.4 (GPB3)
/IO_B4: J8.1, U2.5 (GPB4)
/IO_B5: J8.2, U2.6 (GPB5)
/IO_B6: J8.3, U2.7 (GPB6)
/IO_B7: J8.4, U2.8 (GPB7)
/LED_BOARD_CONN: D4.2 (A), SW1.4
GND: C1.2, C2.2, C3.2, J1.3, J3.3, R1.1, R2.1, R3.1, R4.1, U1.10 (V_{SS}), U1.15 (A0), U1.16 (A1), U1.17 (A2), U2.10 (V_{SS}), U2.16 (A1), U2.17 (A2)
unnamed: D1.1 (K), R1.2
unnamed: D2.1 (K), R2.2
unnamed: D3.1 (K), R3.2
unnamed: D4.1 (K), R4.2
unnamed: J2.5, SW1.6
unnamed: U1.8 (GPB7), U1.21 (GPA0)
unnamed: U1.7 (GPB6), U1.22 (GPA1)
unnamed: U1.6 (GPB5), U1.23 (GPA2)
unnamed: U1.5 (GPB4), U1.24 (GPA3)
unnamed: U1.4 (GPB3), U1.25 (GPA4)
unnamed: U1.3 (GPB2), U1.26 (GPA5)
unnamed: U1.2 (GPB1), U1.27 (GPA6)
unnamed: U1.1 (GPB0), U1.28 (GPA7)

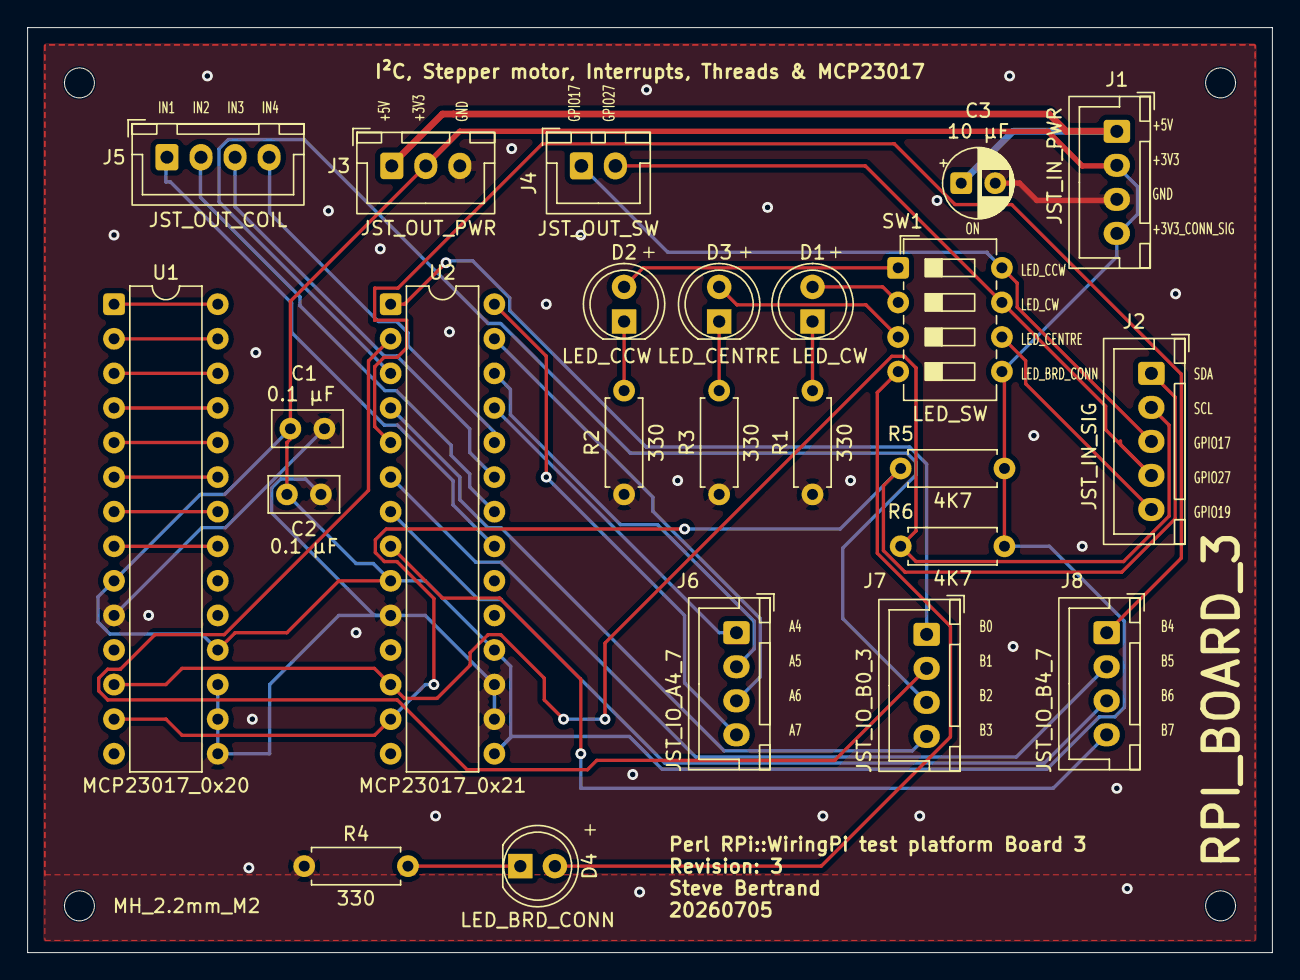
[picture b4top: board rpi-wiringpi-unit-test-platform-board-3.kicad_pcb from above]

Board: 2 copper layers, 91.4 x 67.9 mm, 28 parts (0 on the bottom side), 40 nets.

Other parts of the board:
MH1, MH2, MH3, MH4: MH_2.2mm_M2; MountingHole_2.2mm_M2

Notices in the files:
README:
COPYRIGHT AND LICENSE
Copyright (C) 2016-2026 by Steve Bertrand
